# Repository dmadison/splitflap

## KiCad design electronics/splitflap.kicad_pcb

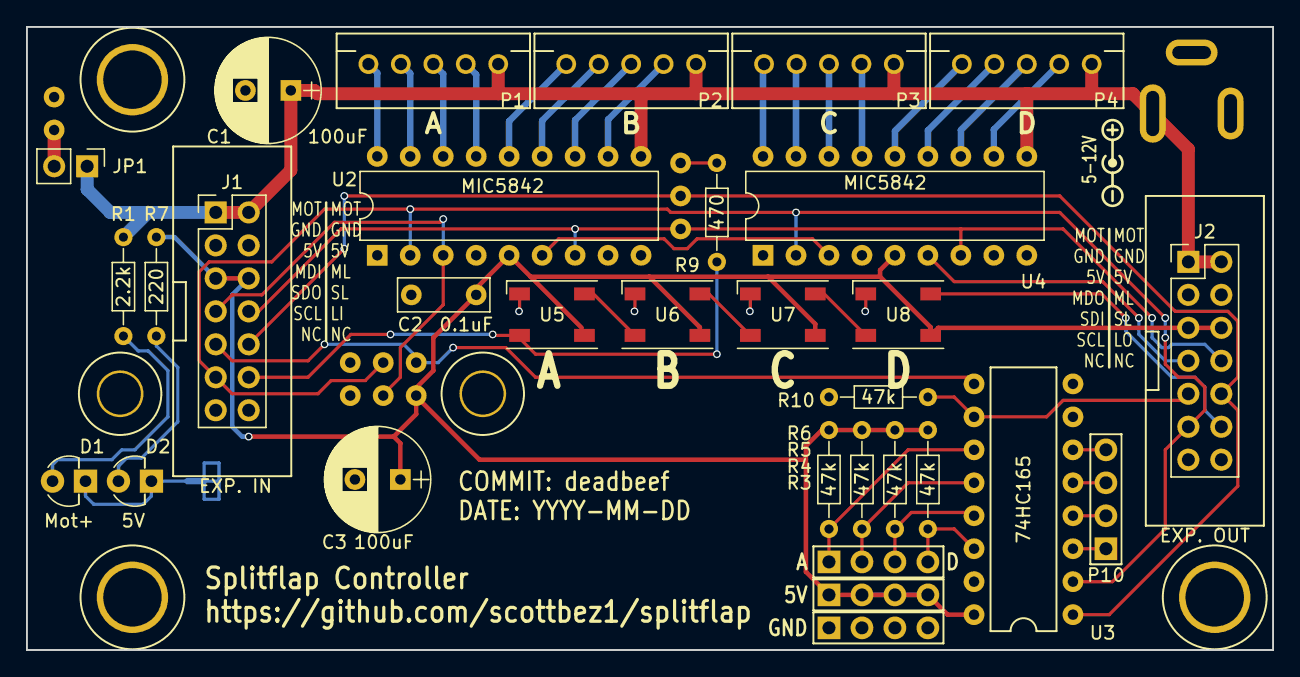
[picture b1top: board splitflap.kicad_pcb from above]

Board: 2 copper layers, 96.0 x 48.0 mm, 38 parts (1 on the bottom side), 45 nets.

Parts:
C1, C3: 100uF; CP_Radial_D8.0mm_P3.50mm
C2: 0.1uF; C_Rect_L7.0mm_W2.5mm_P5.00mm
CON1: MOTOR_PWR; PJ-202A
D1: Mot+; LED_D3.0mm
D2: 5V; LED_D3.0mm
J1: EXP. IN; Pin_Header_Straight_2x07_Pitch2.54mm_IDC_Shrouded
J2: EXP. OUT; Pin_Header_Straight_2x07_Pitch2.54mm_IDC_Shrouded
JP1: VIN <-> VCC; Pin_Header_Straight_1x02_Pitch2.54mm
JP2: LED_Jumper; SolderJumper-2_P1.3mm_Bridged_Pad1.0x1.5mm
P1, P2, P3, P4: CONN_01X05; JST_XH_2-5mm_5pin
P6, P7, P8, P10: CONN_01X04; Pin_Header_Straight_1x04
R1: 2.2k; R_Axial_DIN0204_L3.6mm_D1.6mm_P7.62mm_Horizontal
R3, R4, R5, R6, R10: 47k; R_Axial_DIN0204_L3.6mm_D1.6mm_P7.62mm_Horizontal
R7: 220; R_Axial_DIN0204_L3.6mm_D1.6mm_P7.62mm_Horizontal
R9: 470; R_Axial_DIN0204_L3.6mm_D1.6mm_P7.62mm_Horizontal
U1: arduino_uno_shield
U2, U4: MIC5842; DIP-18_W7.62mm
U3: 74HC165; 74HC165_DIP-16_W7.62mm
U5, U6, U7, U8: WS2812B; LED_WS2812B-PLCC4
Z1, Z2, Z3: MOUNT; M4_mount
Z4: ribbon cable (BOM only); Dummy_Empty

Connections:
+5V: C2.1, C3.1, J1.5, J1.6, J2.5, J2.6, P7.1, P7.2, P7.3, P7.4, R3.1, R4.1, R5.1, R6.1, R7.2, U1.ISP2, U2.5, U3.16, U4.5, U5.1, U6.1, U7.1, U8.1
/DBGLED_IN: J1.12, R9.2, U5.4
/DBGLED_OUT: J2.12, U8.2
/MOTOR_DATA_IN: J1.7, U1.ISP4, U2.3
/MOTOR_DATA_OUT: J2.7, U4.6
/MOTOR_LATCH: J1.8, J2.8, U1.D4, U2.7, U4.7
/SENSE1: P6.1, R6.2, U3.11
/SENSE2: P6.2, R5.2, U3.12
/SENSE3: P6.3, R4.2, U3.13
/SENSE4: P6.4, R3.2, U3.14
/SENSOR_DATA_IN: J2.9, R10.1, U3.10
/SENSOR_DATA_OUT: J1.9, U1.ISP1, U3.9
/SENSOR_LATCH: J1.10, J2.10, U1.D5, U3.1
/SPI_CLOCK: J1.11, J2.11, U1.ISP3, U2.2, U3.2, U4.2
GND: C1.2, C2.2, C3.2, CON1.2, CON1.3, J1.3, J1.4, J2.3, J2.4, JP2.1, P8.1, P8.2, P8.3, P8.4, R10.2, U1.GND, U1.ISP6, U2.1, U2.4, U2.8, U2.9, U3.8, U3.15, U4.1, U4.4, U4.8, U4.9, U5.3, U6.3, U7.3, U8.3, Z1.1, Z2.1, Z3.1
unnamed: D1.1, D2.1, JP2.2
unnamed: D1.2, R1.1
unnamed: D2.2, R7.1
unnamed: JP1.2, U1.VIN
unnamed: P1.1, U2.18
unnamed: P1.2, U2.17
unnamed: P1.3, U2.16
unnamed: P1.4, U2.15
unnamed: P2.1, U2.14
unnamed: P2.2, U2.13
unnamed: P2.3, U2.12
unnamed: P2.4, U2.11
unnamed: P3.1, U4.18
unnamed: P3.2, U4.17
unnamed: P3.3, U4.16
unnamed: P3.4, U4.15
unnamed: P4.1, U4.14
unnamed: P4.2, U4.13
unnamed: P4.3, U4.12
unnamed: P4.4, U4.11
unnamed: P10.1, U3.3
unnamed: P10.2, U3.4
unnamed: P10.3, U3.5
unnamed: P10.4, U3.6
unnamed: R9.1, U1.D6
unnamed: U2.6, U4.3
unnamed: U5.2, U6.4
unnamed: U6.2, U7.4
unnamed: U7.2, U8.4
VCC: C1.1, CON1.1, J1.1, J1.2, J2.1, J2.2, JP1.1, P1.5, P2.5, P3.5, P4.5, R1.2, U2.10, U4.10

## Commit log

2020-09-26 Render assembly with 3.0 thickness
    For the legacy 3.2 thickness value with the real-world panel thickness of 3.0.
2020-09-26 Add test piece functions to SCAD
2020-09-26 Modify text_label module to pass halign
2020-09-27 Add test piece output to generate_2d.py
2020-09-27 Improve test piece module code clarity
2021-03-21 Move power LEDs lower
2021-03-25 CAD: Increase font generator Y spacing (#136)
    For more breathing room and even spacing between the X and Y axes
2021-03-25 Custom firmware settings
2021-07-03 Mounting Brackets (#160)
    Creates `mounting_bracket.scad` which generates geometry for 3D-printable mounting brackets. Two brackets are defined, using the same common base geometry:
    * `mounting_bracket_t_slot` for mounting a module to an M4-sized T-slot, using an M4-12 bolt and matching T-nut.
    * `mounting_bracket_screw_holes` for mounting a module to a wooden board using flat-head M4 screws. The hole for the enclosure's bolt either needs to be undersized for thread engagement or enlarged f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
    The base geometry uses the existing hole in the bottom enclosure piece and juts up against the left and right enclosure sides to prevent the module from twisting.
    Thi
2021-07-18 Classic Driver PCB Mount (#166)
    This is a 3D printable mounting bracket for the "classic" driver PCB. It includes three mounting points for the PCB itself using heat-set inserts, and two screw mounts on either side for securing int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
    ![sf-classic-pcb-mount](https://user-images.githubusercontent.com/24282108/125182112-38add000-e1d9-11eb-9607-914a2b4d920a.png)
    In addition to the mount itself this PR makes some quality of life changes to some of the `shapes` functions, including conditional rounding of corners for both the 2D and 3D rounded square functions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
